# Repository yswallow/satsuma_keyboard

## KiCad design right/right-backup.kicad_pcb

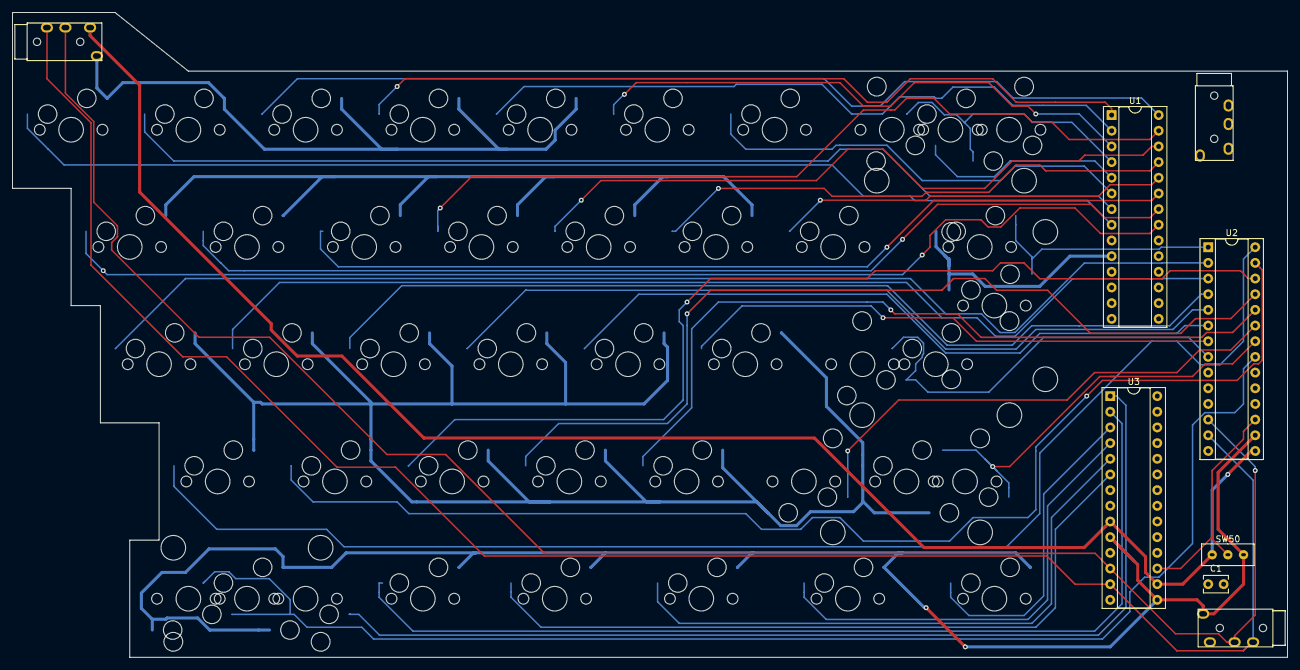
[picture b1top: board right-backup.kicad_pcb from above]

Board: 2 copper layers, 206.6 x 104.5 mm, 51 parts (0 on the bottom side), 43 nets.

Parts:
C1: C; C_Disc_D3.8mm_W2.6mm_P2.50mm
J1, J2, J3: Modulo-Jack; MJ-4PP-9
SW1, SW2, SW3, SW4, SW5, SW6, SW7, SW8, SW9, SW10, SW11, SW12, SW13, SW14, SW15, SW16, SW18, SW19, SW20, SW21, SW22, SW23, SW24, SW25, SW26, SW27, SW28, SW29, SW30, SW32, SW33, SW34: SW_Push; MXOnly-1U-Hotswap
SW17: SW_Push; MXOnly-ISO-HotSwap
SW31: SW_Push; MXOnly-1.75U-Hotswap
SW35, SW36, SW37, SW38: SW_Push; MXOnly-1.25U-Hotswap
SW39: SW_Push; MXOnly-2U-Hotswap
SW40: SW_Push; MXOnly-1.5U-Hotswap
SW41: SW_Push; MXOnly-2.25U-Hotswap
SW42: SW_Push; MXOnly-2.75U-Hotswap
SW43: SW_Push; MXOnly-2U-Hotswap-ReversedStabilizers
SW50: SW_SPDT; SlideSwitch_SS-12D00
U1, U2, U3: MCP23017_SP; DIP-28_W7.62mm_Socket

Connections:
ADDR: SW50.2, U1.17, U2.17, U3.17
GND: C1.2, J1.A, J2.A, J3.A, SW1.2, SW2.2, SW3.2, SW4.2, SW5.2, SW6.2, SW7.2, SW8.2, SW9.1, SW10.2, SW11.2, SW12.2, SW13.2, SW14.2, SW15.2, SW16.2, SW17.1, SW18.2, SW19.2, SW20.2, SW21.2, SW22.2, SW23.2, SW24.2, SW25.2, SW26.2, SW27.2, SW28.2, SW29.2, SW30.2, SW31.2, SW32.2, SW33.2, SW34.2, SW35.2, SW36.2, SW37.2, SW38.2, SW39.2, SW40.1, SW41.2, SW42.1, SW43.2, SW50.3, U1.10, U1.15, U1.16, U2.10, U2.16, U3.10, U3.15
SCK: J1.C, J2.C, J3.C, U1.12, U2.12, U3.12
SDA: J1.B, J2.B, J3.B, U1.13, U2.13, U3.13
SW1: SW1.1, U1.8
SW2: SW2.1, U1.7
SW3: SW3.1, U1.28
SW4: SW4.1, U1.1
SW5: SW5.1, U1.2
SW6: SW6.1, U1.3
SW7: SW7.1, U1.6
SW8: SW8.1, U1.5
SW9: SW9.2, SW39.1, U1.4
SW10: SW10.1, U1.21
SW11: SW11.1, U1.22
SW12: SW12.1, U1.23
SW13: SW13.1, U1.27
SW14: SW14.1, U1.26
SW15: SW15.1, U1.25
SW16: SW16.1, U1.24
SW17: SW17.2, SW40.2, U2.1
SW18: SW18.1, U2.2
SW19: SW19.1, U2.3
SW20: SW20.1, U2.4
SW21: SW21.1, U2.5
SW22: SW22.1, U2.6
SW23: SW23.1, U2.7
SW24: SW24.1, SW41.1, U2.8
SW25: SW25.1, U2.28
SW26: SW26.1, U2.27
SW27: SW27.1, U2.26
SW28: SW28.1, U2.25
SW29: SW29.1, U2.24
SW30: SW30.1, U2.23
SW31: SW31.1, SW42.2, U2.22
SW32: SW32.1, SW43.1, U2.21
SW33: SW33.1, U3.1
SW34: SW34.1, U3.2
SW35: SW35.1, U3.6
SW36: SW36.1, U3.5
SW37: SW37.1, U3.4
SW38: SW38.1, U3.3
VCC: C1.1, J1.D, J2.D, J3.D, SW50.1, U1.9, U2.9, U2.15, U3.9, U3.16
